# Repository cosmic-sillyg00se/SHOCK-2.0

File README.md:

# SHOCK-2.0
(6/25/2025) After some research and finally becoming confident enough to try SMD, this board is much cleaner and more compact! Not that it worked. Renamed to SHOCK as a tribute to Lafayette Systems.

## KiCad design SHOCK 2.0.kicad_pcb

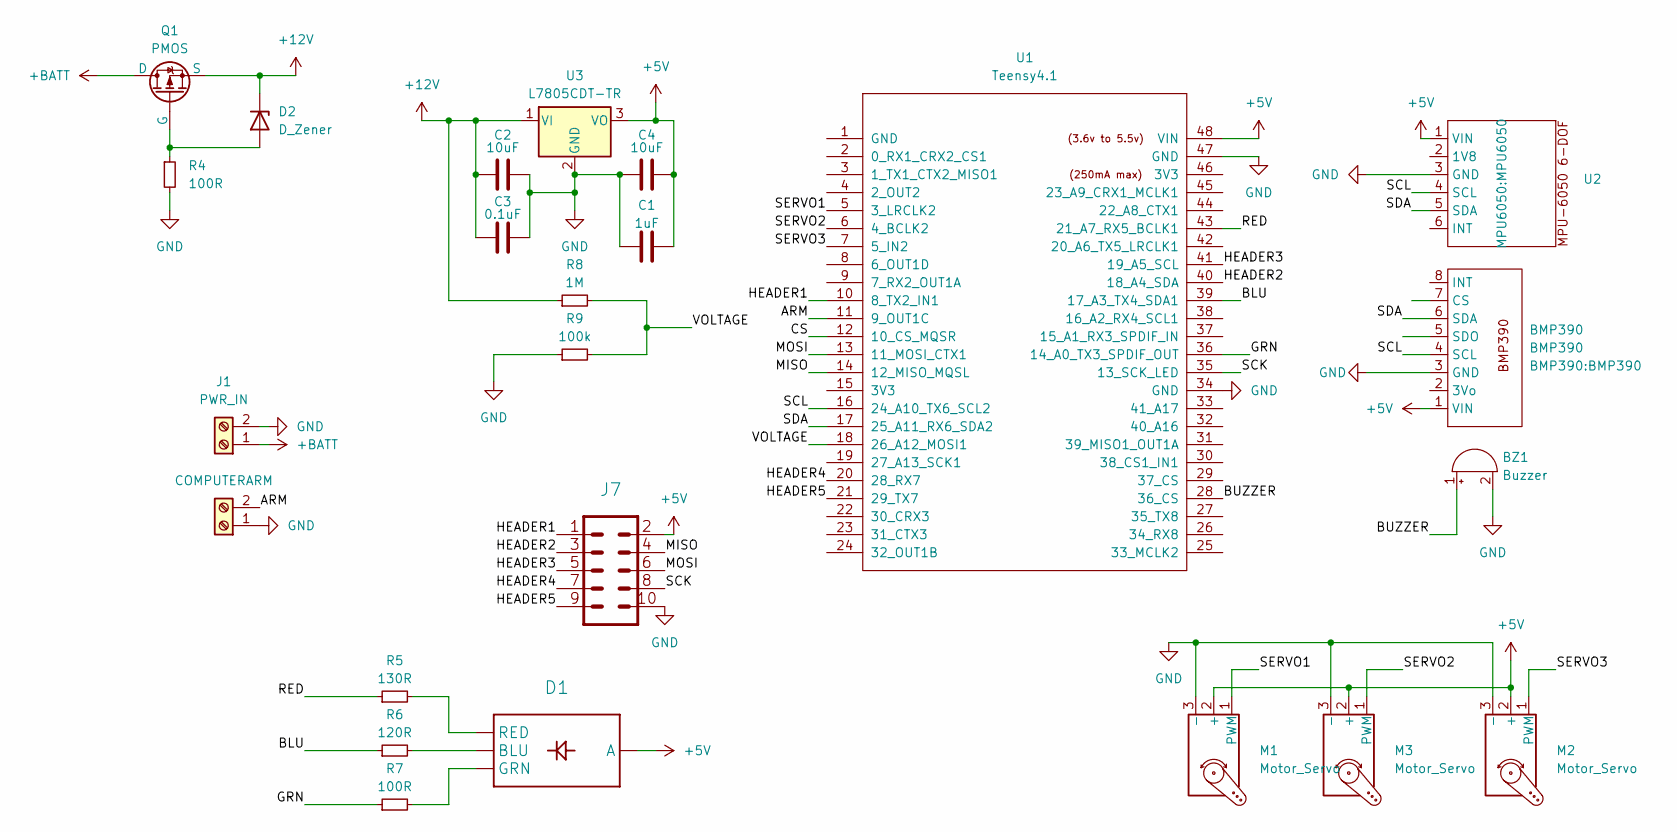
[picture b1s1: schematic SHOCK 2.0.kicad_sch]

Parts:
BMP390: BMP390
BZ1: Buzzer; Buzzer_TDK_PS1240P02BT_D12.2mm_H6.5mm
C1: 1uF; C_1210_3225Metric_Pad1.33x2.70mm_HandSolder
C2, C4: 10uF; C_1210_3225Metric_Pad1.33x2.70mm_HandSolder
C3: 0.1uF; C_1210_3225Metric_Pad1.33x2.70mm_HandSolder
D1: LED_Wurth_150044M155260
D2: D_Zener; D_SOD-123F
J1: PWR_IN; TerminalBlock_MaiXu_MX126-5.0-02P_1x02_P5.00mm
J5: COMPUTERARM; TerminalBlock_MaiXu_MX126-5.0-02P_1x02_P5.00mm
J7: PinHeader_2x05_P2.54mm_Vertical
M1, M2, M3: Motor_Servo; PinHeader_1x03_P2.54mm_Vertical
Q1: PMOS; SOT-23
R4, R7: 100R; R_2010_5025Metric_Pad1.40x2.65mm_HandSolder
R5: 130R; R_2010_5025Metric_Pad1.40x2.65mm_HandSolder
R6: 120R; R_2010_5025Metric_Pad1.40x2.65mm_HandSolder
R8: 1M; R_2010_5025Metric_Pad1.40x2.65mm_HandSolder
R9: 100k; R_2010_5025Metric_Pad1.40x2.65mm_HandSolder
U1: Teensy4.1; Teensy41
U2: MPU6050
U3: L7805CDT-TR; TO-252-2

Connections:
+5V: BMP390.1 (VIN), C1.2, C4.2, D1.2 (A), J7.2, M1.2 (+), M2.2 (+), M3.2 (+), U1.48 (VIN), U2.1 (VIN), U3.3 (VO)
+12V: C2.1, C3.1, D2.1 (K), Q1.3 (S), R8.1, U3.1 (VI)
+BATT: J1.1, Q1.1 (D)
/ARM: J5.2, U1.11 (9_OUT1C)
/BLU: R6.1, U1.39 (17_A3_TX4_SDA1)
/BUZZER: BZ1.1 (+), U1.28 (36_CS)
/CS: U1.12 (10_CS_MQSR)
/GRN: R7.1, U1.36 (14_A0_TX3_SPDIF_OUT)
/HEADER1: J7.1, U1.10 (8_TX2_IN1)
/HEADER2: J7.3, U1.40 (18_A4_SDA)
/HEADER3: J7.5, U1.41 (19_A5_SCL)
/HEADER4: J7.7, U1.20 (28_RX7)
/HEADER5: J7.9, U1.21 (29_TX7)
/MISO: J7.4, U1.14 (12_MISO_MQSL)
/MOSI: J7.6, U1.13 (11_MOSI_CTX1)
/RED: R5.1, U1.43 (21_A7_RX5_BCLK1)
/SCK: J7.8, U1.35 (13_SCK_LED)
/SCL: BMP390.4 (SCL), U1.16 (24_A10_TX6_SCL2), U2.4 (SCL)
/SDA: BMP390.6 (SDA), U1.17 (25_A11_RX6_SDA2), U2.5 (SDA)
/SERVO1: M1.1 (PWM), U1.5 (3_LRCLK2)
/SERVO2: M3.1 (PWM), U1.6 (4_BCLK2)
/SERVO3: M2.1 (PWM), U1.7 (5_IN2)
/VOLTAGE: R8.2, R9.2, U1.18 (26_A12_MOSI1)
GND: BMP390.3 (GND), BZ1.2 (-), C1.1, C2.2, C3.2, C4.1, J1.2, J5.1, J7.10, M1.3 (-), M2.3 (-), M3.3 (-), R4.2, R9.1, U1.34 (GND), U1.47 (GND), U2.3 (GND), U3.2 (GND)
unnamed: D1.4 (BLU), R6.2
unnamed: D1.3 (GRN), R7.2
unnamed: D1.1 (RED), R5.2
unnamed: D2.2 (A), Q1.2 (G), R4.1

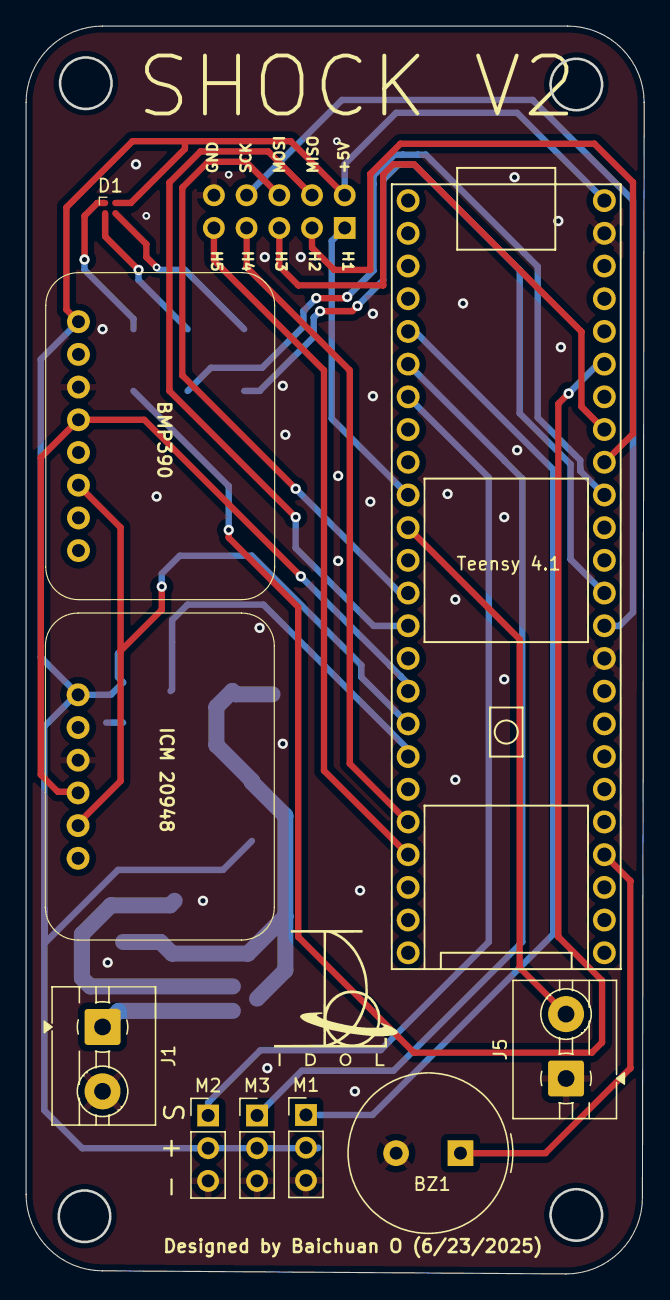
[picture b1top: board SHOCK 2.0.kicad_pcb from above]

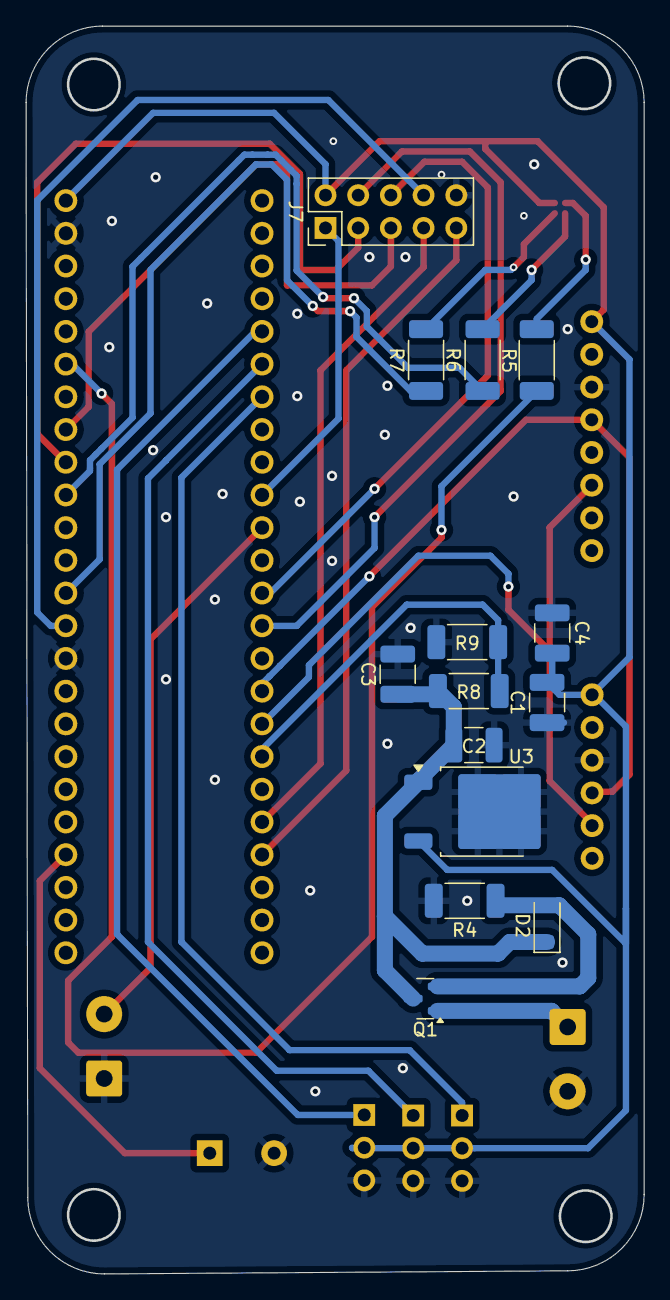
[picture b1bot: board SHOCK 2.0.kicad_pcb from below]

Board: 2 copper layers, 48.0 x 96.9 mm, 24 parts (14 on the bottom side), 27 nets.

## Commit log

2026-02-05 Added all KiCad files
